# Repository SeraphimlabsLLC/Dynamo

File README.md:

# Dynamo
DCC 4 channel booster

ESP32-S3 processor

optocoupled DCC input

4 channels motor shield output with current monitoring. auto reverse possible.

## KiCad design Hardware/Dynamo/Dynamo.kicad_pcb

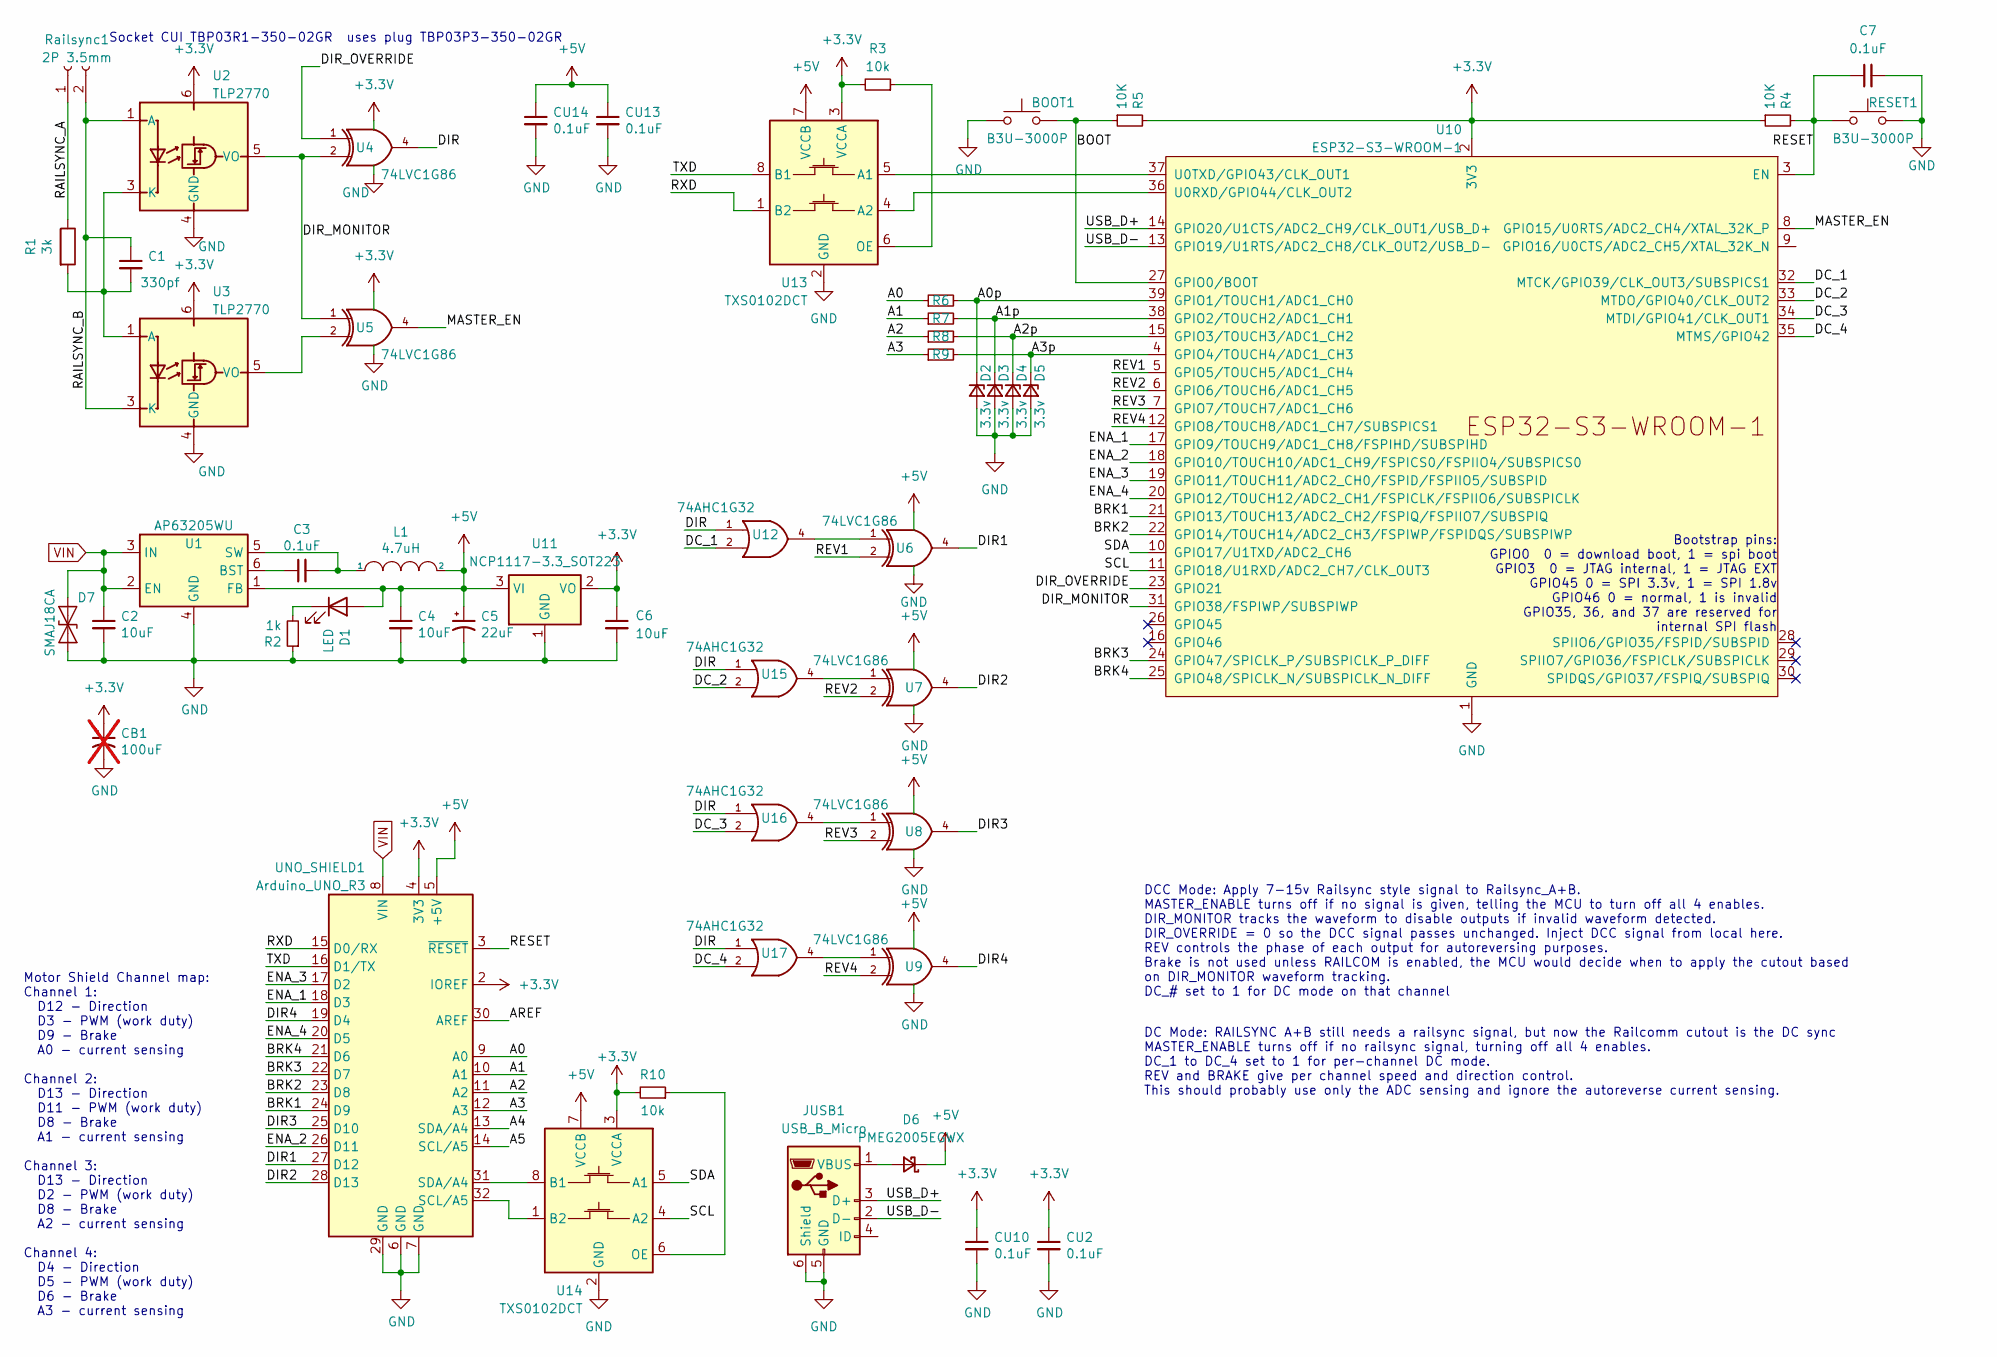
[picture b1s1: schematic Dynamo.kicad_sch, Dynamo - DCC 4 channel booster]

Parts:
BOOT1: B3U-3000P; SW_SPST_B3U-3000P-B; JLCPCB Part # C963349
C1: 330pf; C_1206_3216Metric; JLCPCB Part # C2223641
C2, C4, C6: 10uF; C_1210_3225Metric; JLCPCB Part # C2175202
C3, C7: 0.1uF; C_1206_3216Metric; JLCPCB Part # C600013
C5: 22uF; CP_Elec_5x5.3; JLCPCB Part # C2164091
CB1: 100uF; CP_Radial_D6.3mm_P2.50mm; not fitted
CU2, CU10, CU13, CU14: 0.1uF; C_1206_3216Metric; JLCPCB Part # C600013
D1: LED; LED_1206_3216Metric; JLCPCB Part # C7164018
D2, D3, D4, D5: 3.3v; D_SOD-123; JLCPCB Part # C151564
D6: PMEG2005EGWX; D_SOD-123; JLCPCB Part # C552812
D7: SMAJ18CA; D_SMA; JLCPCB Part # C523217
JUSB1: USB_B_Micro; USB_Micro-B_Molex-105017-0001; JLCPCB Part # C136000
L1: 4.7uH; L_Wurth_WE-LQSH-4020; JLCPCB Part # C2045329
R1: 3k; R_1206_3216Metric; JLCPCB Part # C132648
R2, R6, R7, R8, R9: 1k; R_1206_3216Metric; JLCPCB Part # C131398
R3, R10: 10k; R_1206_3216Metric; JLCPCB Part # C4303232
R4, R5: 10K; R_1206_3216Metric; JLCPCB Part # C4303232
RESET1: B3U-3000P; SW_SPST_B3U-3000P-B; JLCPCB Part # C963349
Railsync1: 2P 3.5mm; PhoenixContact_MC_1,5_2-G-3.5_1x02_P3.50mm_Horizontal; JLCPCB Part # C880572
U1: AP63205WU; TSOT-23-6; JLCPCB Part # C2071056
U2, U3: TLP2770; SO-6L_10x3.84mm_P1.27mm; JLCPCB Part # C150160
U4, U5, U6, U7, U8, U9: 74LVC1G86; SOT-23-5_HandSoldering; JLCPCB Part # C402161
U10: ESP32-S3-WROOM-1; JLCPCB Part # C2980298
U11: NCP1117-3.3_SOT223; SOT-223-3_TabPin2; JLCPCB Part # C91728
U12, U15, U16, U17: 74AHC1G32; SOT-23-5_HandSoldering; JLCPCB Part # C10096
U13, U14: TXS0102DCT; SSOP-8_2.95x2.8mm_P0.65mm; JLCPCB Part # C2677354
UNO_SHIELD1: Arduino_UNO_R3; Arduino_UNO_R3_WithMountingHoles

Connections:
+3.3V: C6.1, CB1.1, CU2.1, CU10.1, R3.2, R4.1, R5.2, R10.2, U2.6, U3.6, U4.5, U5.5, U10.2 (3V3), U11.2 (VO), U13.3 (VCCA), U14.3 (VCCA), UNO_SHIELD1.2 (IOREF), UNO_SHIELD1.4 (3V3)
+5V: C4.1, C5.1, CU13.1, CU14.1, D1.2 (A), D6.1 (K), L1.2, U1.1 (FB), U6.5 (VCC), U7.5 (VCC), U8.5 (VCC), U9.5 (VCC), U11.3 (VI), U12.5 (VCC), U13.7 (VCCB), U14.7 (VCCB), U15.5 (VCC), U16.5 (VCC), U17.5 (VCC), UNO_SHIELD1.5 (+5V)
/A0: R6.1, UNO_SHIELD1.9 (A0)
/A0p: D2.1 (K), R6.2, U10.39 (GPIO1/TOUCH1/ADC1_CH0)
/A1: R7.1, UNO_SHIELD1.10 (A1)
/A1p: D3.1 (K), R7.2, U10.38 (GPIO2/TOUCH2/ADC1_CH1)
/A2: R8.1, UNO_SHIELD1.11 (A2)
/A2p: D4.1 (K), R8.2, U10.15 (GPIO3/TOUCH3/ADC1_CH2)
/A3: R9.1, UNO_SHIELD1.12 (A3)
/A3p: D5.1 (K), R9.2, U10.4 (GPIO4/TOUCH4/ADC1_CH3)
/A4: UNO_SHIELD1.13 (SDA/A4)
/A5: UNO_SHIELD1.14 (SCL/A5)
/AREF: UNO_SHIELD1.30 (AREF)
/BOOT: BOOT1.1, R5.1, U10.27 (GPIO0/BOOT)
/BRK1: U10.21 (GPIO13/TOUCH13/ADC2_CH2/FSPIQ/FSPIIO7/S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), UNO_SHIELD1.24 (D9)
/BRK2: U10.22 (GPIO14/TOUCH14/ADC2_CH3/FSPIWP/FSPIDQS/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), UNO_SHIELD1.23 (D8)
/BRK3: U10.24 (GPIO47/SPICLK_P/SUBSPICLK_P_DIFF), UNO_SHIELD1.22 (D7)
/BRK4: U10.25 (GPIO48/SPICLK_N/SUBSPICLK_N_DIFF), UNO_SHIELD1.21 (D6)
/DC_1: U10.32 (MTCK/GPIO39/CLK_OUT3/SUBSPICS1), U12.2
/DC_2: U10.33 (MTDO/GPIO40/CLK_OUT2), U15.2
/DC_3: U10.34 (MTDI/GPIO41/CLK_OUT1), U16.2
/DC_4: U10.35 (MTMS/GPIO42), U17.2
/DIR: U4.4, U12.1, U15.1, U16.1, U17.1
/DIR1: U6.4, UNO_SHIELD1.27 (D12)
/DIR2: U7.4, UNO_SHIELD1.28 (D13)
/DIR3: U8.4, UNO_SHIELD1.25 (D10)
/DIR4: U9.4, UNO_SHIELD1.19 (D4)
/DIR_MONITOR: U2.5 (VO), U4.2, U5.1, U10.31 (GPIO38/FSPIWP/SUBSPIWP)
/DIR_OVERRIDE: U4.1, U10.23 (GPIO21)
/ENA_1: U10.17 (GPIO9/TOUCH9/ADC1_CH8/FSPIHD/SUBSPIHD), UNO_SHIELD1.18 (D3)
/ENA_2: U10.18 (GPIO10/TOUCH10/ADC1_CH9/FSPICS0/FSPIIO4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), UNO_SHIELD1.26 (D11)
/ENA_3: U10.19 (GPIO11/TOUCH11/ADC2_CH0/FSPID/FSPIIO5/S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), UNO_SHIELD1.17 (D2)
/ENA_4: U10.20 (GPIO12/TOUCH12/ADC2_CH1/FSPICLK/FSPIIO6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), UNO_SHIELD1.20 (D5)
/MASTER_EN: U5.4, U10.8 (GPIO15/U0RTS/ADC2_CH4/XTAL_32K_P)
/RAILSYNC_A: R1.1, Railsync1.1
/RAILSYNC_B: C1.1, Railsync1.2, U2.1 (A), U3.3 (K)
/RESET: C7.1, R4.2, RESET1.2, U10.3 (EN), UNO_SHIELD1.3 (~RESET)
/REV1: U6.2, U10.5 (GPIO5/TOUCH5/ADC1_CH4)
/REV2: U7.2, U10.6 (GPIO6/TOUCH6/ADC1_CH5)
/REV3: U8.2, U10.7 (GPIO7/TOUCH7/ADC1_CH6)
/REV4: U9.2, U10.12 (GPIO8/TOUCH8/ADC1_CH7/SUBSPICS1)
/RXD: U13.1 (B2), UNO_SHIELD1.15 (D0/RX)
/SCL: U10.11 (GPIO18/U1RXD/ADC2_CH7/CLK_OUT3), U14.4 (A2)
/SDA: U10.10 (GPIO17/U1TXD/ADC2_CH6), U14.5 (A1)
/TXD: U13.8 (B1), UNO_SHIELD1.16 (D1/TX)
/USB_D+: JUSB1.3 (D+), U10.14 (GPIO20/U1CTS/ADC2_CH9/CLK_OUT1/USB_D+)
/USB_D-: JUSB1.2 (D-), U10.13 (GPIO19/U1RTS/ADC2_CH8/CLK_OUT2/USB_D-)
GND: BOOT1.2, C2.2, C4.2, C5.2, C6.2, C7.2, CB1.2, CU2.2, CU10.2, CU13.2, CU14.2, D2.2 (A), D3.2 (A), D4.2 (A), D5.2 (A), D7.2 (A2), JUSB1.5 (GND), JUSB1.6 (Shield), R2.1, RESET1.1, U1.4 (GND), U2.4 (GND), U3.4 (GND), U4.3, U5.3, U6.3 (GND), U7.3 (GND), U8.3 (GND), U9.3 (GND), U10.1 (GND), U10.40 (GND), U10.41 (GND), U11.1 (GND), U12.3 (GND), U13.2 (GND), U14.2 (GND), U15.3 (GND), U16.3 (GND), U17.3 (GND), UNO_SHIELD1.6 (GND), UNO_SHIELD1.7 (GND), UNO_SHIELD1.29 (GND)
unnamed: D1.1 (K), R2.2
unnamed: D6.2 (A), JUSB1.1 (VBUS)
unnamed: C3.1, U1.6 (BST)
unnamed: C3.2, L1.1, U1.5 (SW)
unnamed: C1.2, R1.2, U2.3 (K), U3.1 (A)
unnamed: U3.5 (VO), U5.2
unnamed: U10.36 (U0RXD/GPIO44/CLK_OUT2), U13.4 (A2)
unnamed: U10.37 (U0TXD/GPIO43/CLK_OUT1), U13.5 (A1)
unnamed: U6.1, U12.4
unnamed: R3.1, U13.6 (OE)
unnamed: U14.8 (B1), UNO_SHIELD1.31 (SDA/A4)
unnamed: U14.1 (B2), UNO_SHIELD1.32 (SCL/A5)
unnamed: R10.1, U14.6 (OE)
unnamed: U7.1, U15.4
unnamed: U8.1, U16.4
unnamed: U9.1, U17.4
VIN: C2.1, D7.1 (A1), U1.2 (EN), U1.3 (IN), UNO_SHIELD1.8 (VIN)

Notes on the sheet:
Bootstrap pins: GPIO0 0 = download boot, 1 = spi boot GPIO3 0 = JTAG internal, 1 = JTAG EXT GPIO45 0 = SPI 3.3v, 1 = SPI 1.8v GPIO46 0 = normal, 1 is invalid GPIO35, 36, and 37 are reserved for internal SPI flash
DC Mode: RAILSYNC A+B still needs a railsync signal, but now the Railcomm cutout is the DC sync MASTER_ENABLE turns off if no railsync signal, turning off all 4 enables. DC_1 to DC_4 set to 1 for per-channel DC mode. REV and BRAKE give per channel speed and direction control. This should probably u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
Socket CUI TBP03R1-350-02GR uses plug TBP03P3-350-02GR
DCC Mode: Apply 7-15v Railsync style signal to Railsync_A+B. MASTER_ENABLE turns off if no signal is given, telling the MCU to turn off all 4 enables. DIR_MONITOR tracks the waveform to disable outputs if invalid waveform detected. DIR_OVERRIDE = 0 so the DCC signal passes unchanged. Inject DCC sig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
Motor Shield Channel map: Channel 1: D12 - Direction D3 - PWM (work duty) D9 - Brake A0 - current sensing Channel 2: D13 - Direction D11 - PWM (work duty) D8 - Brake A1 - current sensing Channel 3: D13 - Direction D2 - PWM (work duty) D8 - Brake A2 - current sensing Channel 4: D4 - Direction D5 - P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

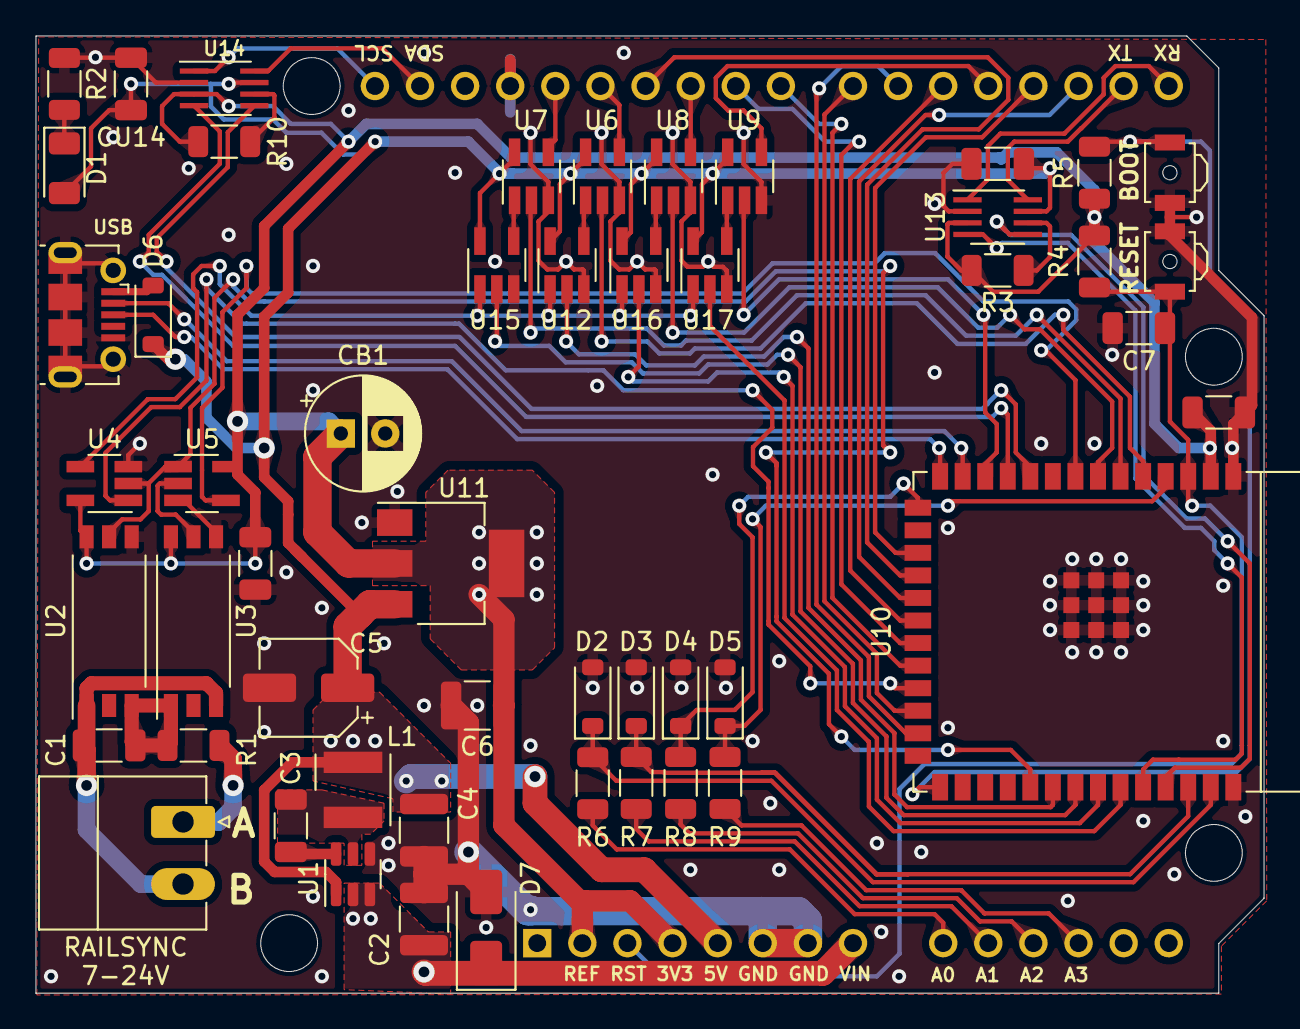
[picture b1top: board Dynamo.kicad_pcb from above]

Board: 2 copper layers, 69.2 x 53.9 mm, 52 parts (1 on the bottom side), 62 nets.

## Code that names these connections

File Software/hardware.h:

//ADC Settings:
#DEFINE ADC_DMAX 4095 //4095 in single shot, 8191 in continuous
#DEFINE ADC_VMAX 3.1 //Max readable voltage is actually 3.1v using mode ADC_ATTEN_DB_11  

//TTY settings:
/* Pin Map
TXD = GPIO43(U0TXD)
RXD = GPIO44(U0RXD)
*/
#DEFINE TTY_TX_BUFF = 4096
#DEFINE TTY_RX_BUFF = 4096

//I2C settings: 
/* Pin Map
SDA = GPIO17
SCL = GPIO18
*/
#DEFINE I2C_TX_BUFF = 4096
#DEFINE I2C_RX_BUFF = 4096

//Loconet settings:
/* Pin Map
LN_TX = GPIO17(U1RXD)
LN_RX = GPIO18 (U1RXD)
LN_COLL = GPIO0
*/
#DEFINE LN_TX_BUFF = 4096
#DEFINE LN_RX_BUFF = 4096

//Booster Control IO
/* Pin Map
DIR_MONITOR = GPIO38
DIR_OVERRIDE = GPIO21
MASTER_EN = GPIO15
*/

//Track 1 output
/*  Pin Map
ENA_1 = GPIO9
REV_1 = GPIO6
BRK_1 = GPIO13
A1 = GPIO1(ADC1_CH0)
*/
#DEFINE OUT1_MAX_A 4090 //ADC_DMAX / ADC_VMAX * SENSE_V

//Track 2 output
/* Pin Map
ENA_2 = GPIO10
REV_2 = GPIO7
BRK_2 = GPIO14
A2 = GPIO2(ADC1_CH1)
*/
#DEFINE OUT2_MAX_A 4090 //ADC_DMAX / ADC_VMAX * SENSE_V

//Track 3 output
/* Pin Map
ENA_3 = GPIO11
REV_3 = GPIO8
BRK_3 = GPIO47
A3 = GPIO2(ADC1_CH2)
*/
#DEFINE OUT3_MAX_A 4090 //ADC_DMAX / ADC_VMAX * SENSE_V

//Track 3 output
/* Pin Map
ENA_4 = GPIO12
REV_4 = GPIO9
BRK_4 = GPIO48
A4 = GPIO2(ADC1_CH3)
*/
#DEFINE OUT2_MAX_A 4090 //ADC_DMAX / ADC_VMAX * SENSE_V

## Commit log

2023-07-27 added hardware details to README.md
2023-07-27 Update README.md
    Fixed formatting
2023-07-27 Folder structure for hardware/software and KiCad solution
2023-07-30 Completed BOM, minor changes to schematic and PCB
2023-08-02 Fixed i2c_init, added rmt_rx_init and rmt_tx_init. Consider making a class arch( to hold all this HAL stuff
2023-08-05 Progress on perhiperal initialization and base structure
2023-08-20 Revised L1 for possible 2A output, cleaner fill zones, fabrication outputs
2023-08-21 Added note about railsync terminal plug, BOM cleanup.
2023-08-27 Initial .gitignore
2023-08-27 TrackChannel struct + extern in main working, MAX_TRACKS not accessible in main
2023-08-27 Temporarially remove conflicting .gitignore
2023-08-27 Pin config situated. track configuration, powermode, and powerstate all written. Still needs the ADC and control signals written.
2023-09-28 First build using ESP AT Firmware 3.2
2023-09-28 Revert "First build using ESP AT Firmware 3.2"
    This reverts commit 2ba02e208466683df0494a767deb1f87a5861263.
2023-11-06 Assembled 1st board. Found Master Enable is too sensitive, the transition period between DCC pulses causes it to read 0 briefly.
2023-11-06 Added configurable (4uS default) deglitch to Master Enable
2023-11-26 Checkpoint
2023-12-17 Schematic features changed: Added USB power for programming, per-track DC mode gating. New PCB layout improving on previous builds.
2023-12-17 Final cleanup, added tags for JLCPCB Fabrication
2023-12-31 Recheck Schematic/PCB for inconsistencies
2024-01-10 Change Railsync input to use same 3.5mm connector as EX8874 outputs
2024-01-14 Revised 5v regulator, layout refinement.
2024-01-30 BOM fix, replace NCP1117 with TLV1117
